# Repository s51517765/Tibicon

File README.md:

# Tibicon

## 概要 (Overview)

ATtiny202 を使ったマイコンボードで、コンセプトとしては小サイズ・低コストで、サイズは 19.0mm x 14.0mm となっています（バリを除く）。2024 年現在、市販されている Arduino 互換機の中で最小です（作者調べ）。

PCB 基板のほかに必要な部品コストは 170 円ほどです（秋月電子価格、送料を除く）。

### ピンアサイン

※書き込み用の UPDI_TX、UPDI_RX と Serial 通信用の TX(GPIO0)、RX(GPIO1)があります。

## 動作要件 (Requirements)

Arduino IDE
<br>　 Arduino IDE 1 系/2 系で動作確認済み
<br>ただし、ライブラリによっては動作しないものもあります。<br>
RAM が小さいので大規模なプログラムには向きません。

書き込みや Serial Print を使用するには USB シリアル変換モジュールが必要です。

## 部品リスト（Parts list）

| 部品                         | 種類           | 秋月コード           | 数量 |
| ---------------------------- | -------------- | -------------------- | ---- |
| 本 PCB                       | -              | -                    | 1    |
| AVR マイコン ATtiny202       | ATTINY202-SSNR | 115731               | 1    |
| ショットキーバリアダイオード | RB160M-30TR    | 101398               | 1    |
| 1608 抵抗                    | 1kΩ            | 111790               | 2    |
| 1608 抵抗                    | 470Ω           | 106471               | 1    |
| 1608LED                      | Green          | 111878               | 1    |
| 1608LED                      | Red            | 111879               | 1    |
| ピンヘッダ                   | オスまたはメス | 105779 または 100167 | 5x2  |

※ただし、抵抗は Amazon などでセットになったものを入手するほうが安いです

## 回路図（Schematics）

## 組み立て方 (Build guide)

LED とショットキーバリアダイオードは極性があります。
<br>抵抗は極性はありません。
<br>マイコン(ATtiny202)は 1 番ピンの向きに注意してください。

ピンヘッダは好みに応じて、メスピン・オスピン、上向き・下向きが選択可能です。
<br>ピンヘッダをはんだ付けするときは基板に対して垂直になるように気をつけてください。ピン 1 本だけ仮ではんだ付けをして正しく接触していることを確認するとよいです。

## 書き込み方法 (Writing method)

ATtiny202 を使用した本マイコンボードは、シリアル UPDI または jtag2updi で書き込みが可能ですが、本プロジェクトではシリアル UPDI を前提として設計しており、こちらを推奨します。
<br>※jtag2updi でも使用可能ですが、外付けの抵抗が必要です。
<br>　以下はシリアル UPDI での書き込み方法です。

### 書き込み時の接続

| 本マイコンボード | シリアル USB |
| ---------------- | ------------ |
| UPDI_TX          | TX ※         |
| UPDI_RX          | RX ※         |
| VCC              | VCC          |
| GND              | GND          |

### 書き込み手順

1.　 Arduino IDE のメニュー「ファイル ¥ 環境設定」より追加のボードマネージャに URL に「http://drazzy.com/package_drazzy.com_index.json」 を追加します。

2.　「ツール ¥ ボードマネージャ」より、「megaTinyCore」を追加します。

3.　「ツール」より、ボード情報を

- ボード:ATtiny412/402/212/202
- Chip:ATtiny202
- 書き込み装置:SerialUPDI - SLOW:57600 baud
  <br>のように変更します。

4.　メニューの「スケッチ ¥ 書き込み装置を使って書き込む」でスケッチを書き込みます。

Arduino IDE の 1 系ではいつもと同じようにスケッチを書き込みボタンを押下でも書き込むことが可能です。

## 使い方 (How to cording)

### L チカ

基本は Arduino と同様に使用できます。
<br>Builtin_LED（基板上の赤 LED）はピン番号 1 で使用できます。
<br>※緑 LED は電源ランプで、通電時に点灯します。

```
void setup() {
  pinMode(1, OUTPUT);
}

void loop() {
  digitalWrite(1, LOW);
  delay(1000);
  digitalWrite(1, HIGH);
  delay(1000);
}
```

ピン番号（GPIO）は 0 ～ 4 が使用可能です。

### PWM

本基板では GPIO0 ～ GPIO4 で PWM が使用できます。
<br>GPIO1 ～ GPIO04では通常の Arduino と同じ使い方で使用できますが、GPIO0 では以下のようにコーディングします。

```
void setup() {
  //GPIO0のセットアップ
  pinMode(0, OUTPUT);
  TCB0.CTRLA = TCB_ENABLE_bm | TCB_CLKSEL_CLKDIV1_gc; //start the timer, set the prescaler to 1
  TCB0.CTRLB = TCB_CCMPEN_bm | TCB_CNTMODE_PWM8_gc; //enable WO0, select the 8 bits PWM mode
  TCB0.CCMPL = 255; //set the PWM resolution to 8 bits
  TCB0.CCMPH = 0; //set the duty cycle
  //GPIO3のセットアップ
  pinMode(3, OUTPUT);
}

void loop()
{
  for (int i = 0; i < 256; i++)
  {
    //GPIO0のPWM
    TCB0.CCMPH = i;
    //GPIO3のPWM
    analogWrite(3,i);
    delay(10);
  }
}
```

### ADC(Analog Read)

本基板では GPIO1 ～ GPIO4 で ADC が使用できます。
<br>通常の Arduino と同じ使い方で使用できます。

```
void setup() {
  pinMode(1, OUTPUT);
  pinMode(4, INPUT);
}

void loop() {
  //ADC は1,2,3,4が使用可能
  int adc = analogRead(4);
  analogWrite(1, adc);
}
```

### Serial print の使い方

USB シリアル変換は内蔵していませんので、外部の USB シリアル変換を使います。

#### USB シリアル使用時の接続

| 本マイコンボード | シリアル USB |
| ---------------- | ------------ |
| TX(GPIO0)        | RX           |
| RX(GPIO1)        | TX           |

※図は基板電源をUSBシリアルから給電する場合

Teraterm などで読み取ることができます。Arduino IDE でも読み取ることはできますが、書き込み時と接続が異なりますので USB シリアルの繋ぎ変えが必要になります。
<br>※D1 ピン（Builtin LED）と D2 ピンを共有しているため Serial と同時に使うことはできません。

## サンプルコード（Sample Code）

[sample フォルダ](/sample/)を参照ください。

## ブートローダーの書き込み (How to write bootloader)

マイコンがおかしくなった時やブートローダーが書き込まれていないマイコンを購入した場合は書き込みが必要になります。Arduino IDE で書き込むことが出来ます。
<br>通常は必要ありません。

## ライセンス (License)

This software is released under the MIT License, see LICENSE.

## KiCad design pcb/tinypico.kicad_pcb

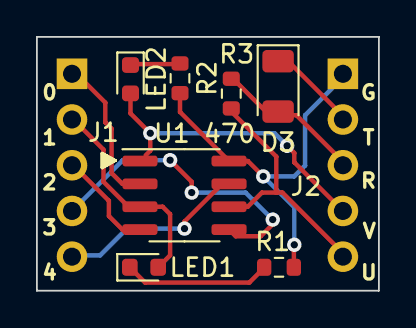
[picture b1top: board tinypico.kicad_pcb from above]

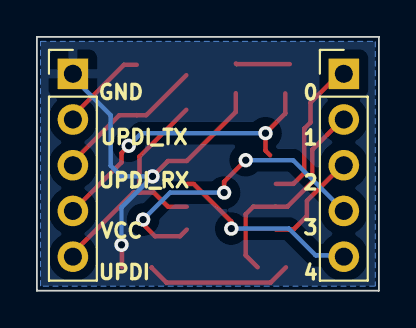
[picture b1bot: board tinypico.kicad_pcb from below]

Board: 2 copper layers, 19.0 x 14.1 mm, 9 parts (2 on the bottom side), 12 nets.

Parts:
470: R3; R_0603_1608Metric
D3: RB160M-30; D_1206_3216Metric
J1, J2: Conn_01x05_Pin; PinHeader_1x05_P2.54mm_Vertical
LED1: LED_G; D_0603_1608Metric
LED2: LED_R; D_0603_1608Metric
R1, R2: 1k; R_0603_1608Metric
U1: ATtiny202-SS; SOIC-8_3.9x4.9mm_P1.27mm

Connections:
1: J2.4, LED2.2 (A), U1.1 (VCC)
2: J1.1, U1.2 (PA6)
3: J1.2, LED1.2 (A), U1.3 (PA7)
4: J1.3, U1.4 (PA1)
5: J1.4, U1.5 (PA2)
6: 470.1, J2.5, U1.6 (~RESET/PA0)
7: J1.5, U1.7 (PA3)
8: J2.1, R1.2, R2.2, U1.8 (GND)
unnamed: LED1.1 (K), R1.1
unnamed: LED2.1 (K), R2.1
UPDI_RX: 470.2, D3.2 (A), J2.3
UPDI_TX: D3.1 (K), J2.2

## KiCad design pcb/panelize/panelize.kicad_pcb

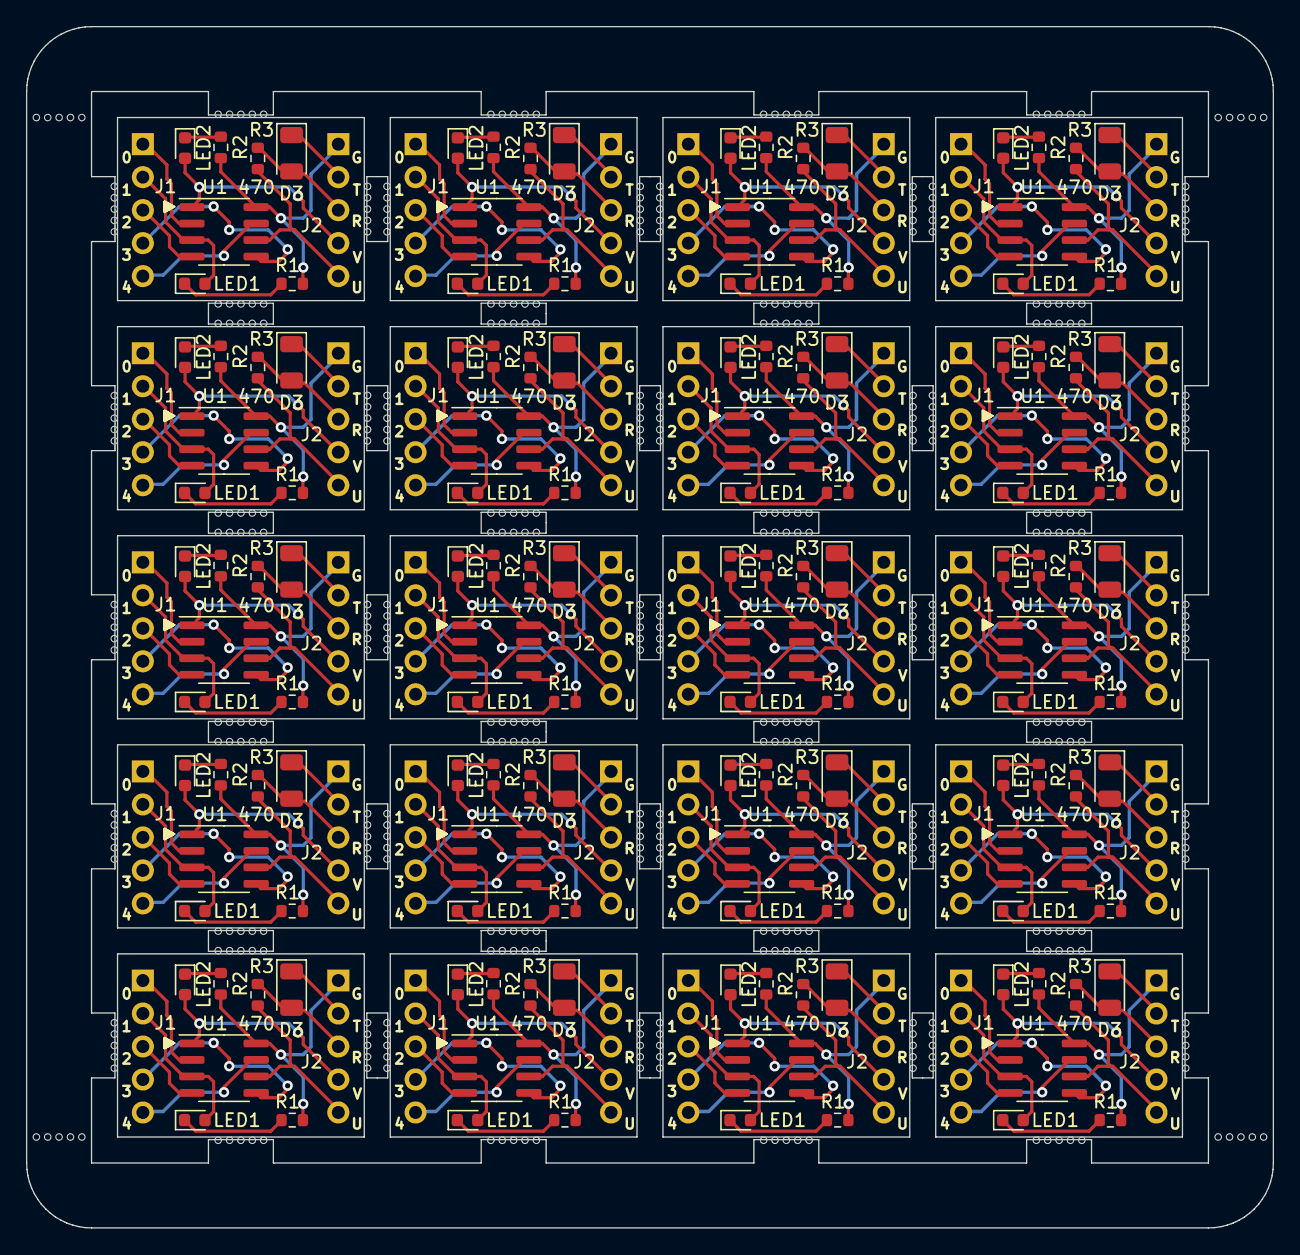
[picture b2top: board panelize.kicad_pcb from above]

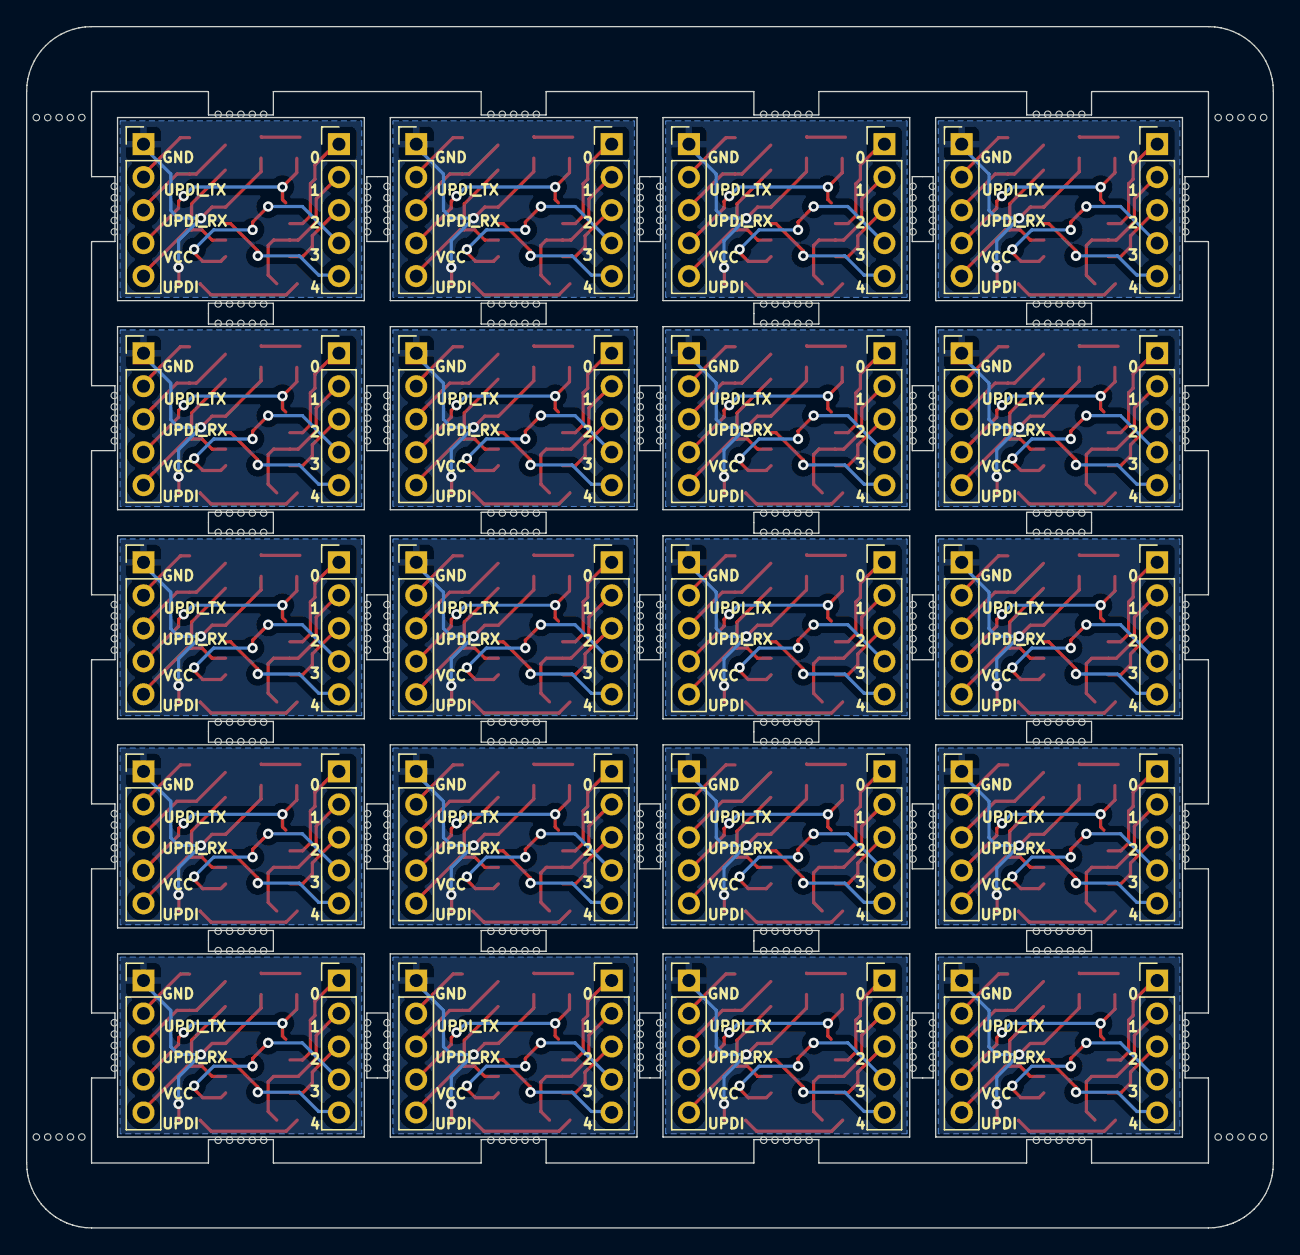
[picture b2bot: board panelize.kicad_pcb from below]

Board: 2 copper layers, 96.0 x 92.5 mm, 600 parts (40 on the bottom side), 240 nets.

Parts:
470, 470#2, 470#3, 470#4, 470#5, 470#6, 470#7, 470#8, 470#9, 470#10, 470#11, 470#12, 470#13, 470#14, 470#15, 470#16, 470#17, 470#18, 470#19, 470#20: R3; R_0603_1608Metric
D3, D3#2, D3#3, D3#4, D3#5, D3#6, D3#7, D3#8, D3#9, D3#10, D3#11, D3#12, D3#13, D3#14, D3#15, D3#16, D3#17, D3#18, D3#19, D3#20: RB160M-30; D_1206_3216Metric
J1, J1#2, J1#3, J1#4, J1#5, J1#6, J1#7, J1#8, J1#9, J1#10, J1#11, J1#12, J1#13, J1#14, J1#15, J1#16, J1#17, J1#18, J1#19, J1#20, J2, J2#2, J2#3, J2#4, J2#5, J2#6, J2#7, J2#8, J2#9, J2#10, J2#11, J2#12, J2#13, J2#14, J2#15, J2#16, J2#17, J2#18, J2#19, J2#20: Conn_01x05_Pin; PinHeader_1x05_P2.54mm_Vertical
KiKit_MB_1_3, KiKit_MB_1_4, KiKit_MB_1_5, KiKit_MB_1_6, KiKit_MB_1_7, KiKit_MB_2_3, KiKit_MB_2_4, KiKit_MB_2_5, KiKit_MB_2_6, KiKit_MB_2_7, KiKit_MB_3_3, KiKit_MB_3_4, KiKit_MB_3_5, KiKit_MB_3_6, KiKit_MB_3_7, KiKit_MB_4_3, KiKit_MB_4_4, KiKit_MB_4_5, KiKit_MB_4_6, KiKit_MB_4_7, KiKit_MB_5_3, KiKit_MB_5_4, KiKit_MB_5_5, KiKit_MB_5_6, KiKit_MB_5_7, KiKit_MB_6_3, KiKit_MB_6_4, KiKit_MB_6_5, KiKit_MB_6_6, KiKit_MB_6_7, KiKit_MB_7_3, KiKit_MB_7_4, KiKit_MB_7_5, KiKit_MB_7_6, KiKit_MB_7_7, KiKit_MB_8_3, KiKit_MB_8_4, KiKit_MB_8_5, KiKit_MB_8_6, KiKit_MB_8_7, KiKit_MB_9_3, KiKit_MB_9_4, KiKit_MB_9_5, KiKit_MB_9_6, KiKit_MB_9_7, KiKit_MB_10_3, KiKit_MB_10_4, KiKit_MB_10_5, KiKit_MB_10_6, KiKit_MB_10_7, KiKit_MB_11_3, KiKit_MB_11_4, KiKit_MB_11_5, KiKit_MB_11_6, KiKit_MB_11_7, KiKit_MB_12_3, KiKit_MB_12_4, KiKit_MB_12_5, KiKit_MB_12_6, KiKit_MB_12_7, KiKit_MB_13_3, KiKit_MB_13_4, KiKit_MB_13_5, KiKit_MB_13_6, KiKit_MB_13_7, KiKit_MB_14_3, KiKit_MB_14_4, KiKit_MB_14_5, KiKit_MB_14_6, KiKit_MB_14_7, KiKit_MB_15_3, KiKit_MB_15_4, KiKit_MB_15_5, KiKit_MB_15_6, KiKit_MB_15_7, KiKit_MB_16_3, KiKit_MB_16_4, KiKit_MB_16_5, KiKit_MB_16_6, KiKit_MB_16_7, KiKit_MB_17_3, KiKit_MB_17_4, KiKit_MB_17_5, KiKit_MB_17_6, KiKit_MB_17_7, KiKit_MB_18_3, KiKit_MB_18_4, KiKit_MB_18_5, KiKit_MB_18_6, KiKit_MB_18_7, KiKit_MB_19_3, KiKit_MB_19_4, KiKit_MB_19_5, KiKit_MB_19_6, KiKit_MB_19_7, KiKit_MB_20_3, KiKit_MB_20_4, KiKit_MB_20_5, KiKit_MB_20_6, KiKit_MB_20_7, KiKit_MB_21_3, KiKit_MB_21_4, KiKit_MB_21_5, KiKit_MB_21_6, KiKit_MB_21_7, KiKit_MB_22_3, KiKit_MB_22_4, KiKit_MB_22_5, KiKit_MB_22_6, KiKit_MB_22_7, KiKit_MB_23_3, KiKit_MB_23_4, KiKit_MB_23_5, KiKit_MB_23_6, KiKit_MB_23_7, KiKit_MB_24_3, KiKit_MB_24_4, KiKit_MB_24_5, KiKit_MB_24_6, KiKit_MB_24_7, KiKit_MB_25_3, KiKit_MB_25_4, KiKit_MB_25_5, KiKit_MB_25_6, KiKit_MB_25_7, KiKit_MB_26_3, KiKit_MB_26_4, KiKit_MB_26_5, KiKit_MB_26_6, KiKit_MB_26_7, KiKit_MB_27_3, KiKit_MB_27_4, KiKit_MB_27_5, KiKit_MB_27_6, KiKit_MB_27_7, KiKit_MB_28_3, KiKit_MB_28_4, KiKit_MB_28_5, KiKit_MB_28_6, KiKit_MB_28_7, KiKit_MB_29_3, KiKit_MB_29_4, KiKit_MB_29_5, KiKit_MB_29_6, KiKit_MB_29_7, KiKit_MB_30_3, KiKit_MB_30_4, KiKit_MB_30_5, KiKit_MB_30_6, KiKit_MB_30_7, KiKit_MB_31_3, KiKit_MB_31_4, KiKit_MB_31_5, KiKit_MB_31_6, KiKit_MB_31_7, KiKit_MB_32_3, KiKit_MB_32_4, KiKit_MB_32_5, KiKit_MB_32_6, KiKit_MB_32_7, KiKit_MB_33_3, KiKit_MB_33_4, KiKit_MB_33_5, KiKit_MB_33_6, KiKit_MB_33_7, KiKit_MB_34_3, KiKit_MB_34_4, KiKit_MB_34_5, KiKit_MB_34_6, KiKit_MB_34_7, KiKit_MB_35_3, KiKit_MB_35_4, KiKit_MB_35_5, KiKit_MB_35_6, KiKit_MB_35_7, KiKit_MB_36_3, KiKit_MB_36_4, KiKit_MB_36_5, KiKit_MB_36_6, KiKit_MB_36_7, KiKit_MB_37_3, KiKit_MB_37_4, KiKit_MB_37_5, KiKit_MB_37_6, KiKit_MB_37_7, KiKit_MB_38_3, KiKit_MB_38_4, KiKit_MB_38_5, KiKit_MB_38_6, KiKit_MB_38_7, KiKit_MB_39_3, KiKit_MB_39_4, KiKit_MB_39_5, KiKit_MB_39_6, KiKit_MB_39_7, KiKit_MB_40_3, KiKit_MB_40_4, KiKit_MB_40_5, KiKit_MB_40_6, KiKit_MB_40_7, KiKit_MB_41_3, KiKit_MB_41_4, KiKit_MB_41_5, KiKit_MB_41_6, KiKit_MB_41_7, KiKit_MB_42_3, KiKit_MB_42_4, KiKit_MB_42_5, KiKit_MB_42_6, KiKit_MB_42_7, KiKit_MB_43_3, KiKit_MB_43_4, KiKit_MB_43_5, KiKit_MB_43_6, KiKit_MB_43_7, KiKit_MB_44_3, KiKit_MB_44_4, KiKit_MB_44_5, KiKit_MB_44_6, KiKit_MB_44_7, KiKit_MB_45_3, KiKit_MB_45_4, KiKit_MB_45_5, KiKit_MB_45_6, KiKit_MB_45_7, KiKit_MB_46_3, KiKit_MB_46_4, KiKit_MB_46_5, KiKit_MB_46_6, KiKit_MB_46_7, KiKit_MB_47_3, KiKit_MB_47_4, KiKit_MB_47_5, KiKit_MB_47_6, KiKit_MB_47_7, KiKit_MB_48_3, KiKit_MB_48_4, KiKit_MB_48_5, KiKit_MB_48_6, KiKit_MB_48_7, KiKit_MB_49_3, KiKit_MB_49_4, KiKit_MB_49_5, KiKit_MB_49_6, KiKit_MB_49_7, KiKit_MB_50_3, KiKit_MB_50_4, KiKit_MB_50_5, KiKit_MB_50_6, KiKit_MB_50_7, KiKit_MB_51_3, KiKit_MB_51_4, KiKit_MB_51_5, KiKit_MB_51_6, KiKit_MB_51_7, KiKit_MB_52_3, KiKit_MB_52_4, KiKit_MB_52_5, KiKit_MB_52_6, KiKit_MB_52_7, KiKit_MB_53_3, KiKit_MB_53_4, KiKit_MB_53_5, KiKit_MB_53_6, KiKit_MB_53_7, KiKit_MB_54_3, KiKit_MB_54_4, KiKit_MB_54_5, KiKit_MB_54_6, KiKit_MB_54_7, KiKit_MB_55_3, KiKit_MB_55_4, KiKit_MB_55_5, KiKit_MB_55_6, KiKit_MB_55_7, KiKit_MB_56_3, KiKit_MB_56_4, KiKit_MB_56_5, KiKit_MB_56_6, KiKit_MB_56_7, KiKit_MB_57_3, KiKit_MB_57_4, KiKit_MB_57_5, KiKit_MB_57_6, KiKit_MB_57_7, KiKit_MB_58_3, KiKit_MB_58_4, KiKit_MB_58_5, KiKit_MB_58_6, KiKit_MB_58_7, KiKit_MB_59_3, KiKit_MB_59_4, KiKit_MB_59_5, KiKit_MB_59_6, KiKit_MB_59_7, KiKit_MB_60_3, KiKit_MB_60_4, KiKit_MB_60_5, KiKit_MB_60_6, KiKit_MB_60_7, KiKit_MB_61_3, KiKit_MB_61_4, KiKit_MB_61_5, KiKit_MB_61_6, KiKit_MB_61_7, KiKit_MB_62_3, KiKit_MB_62_4, KiKit_MB_62_5, KiKit_MB_62_6, KiKit_MB_62_7, KiKit_MB_63_3, KiKit_MB_63_4, KiKit_MB_63_5, KiKit_MB_63_6, KiKit_MB_63_7, KiKit_MB_64_3, KiKit_MB_64_4, KiKit_MB_64_5, KiKit_MB_64_6, KiKit_MB_64_7, KiKit_MB_65_3, KiKit_MB_65_4, KiKit_MB_65_5, KiKit_MB_65_6, KiKit_MB_65_7, KiKit_MB_66_3, KiKit_MB_66_4, KiKit_MB_66_5, KiKit_MB_66_6, KiKit_MB_66_7, KiKit_MB_67_3, KiKit_MB_67_4, KiKit_MB_67_5, KiKit_MB_67_6, KiKit_MB_67_7, KiKit_MB_68_3, KiKit_MB_68_4, KiKit_MB_68_5, KiKit_MB_68_6, KiKit_MB_68_7, KiKit_MB_69_3, KiKit_MB_69_4, KiKit_MB_69_5, KiKit_MB_69_6, KiKit_MB_69_7, KiKit_MB_70_3, KiKit_MB_70_4, KiKit_MB_70_5, KiKit_MB_70_6, KiKit_MB_70_7, KiKit_MB_71_3, KiKit_MB_71_4, KiKit_MB_71_5, KiKit_MB_71_6, KiKit_MB_71_7, KiKit_MB_72_3, KiKit_MB_72_4, KiKit_MB_72_5, KiKit_MB_72_6, KiKit_MB_72_7, KiKit_MB_73_3, KiKit_MB_73_4, KiKit_MB_73_5, KiKit_MB_73_6, KiKit_MB_73_7, KiKit_MB_74_3, KiKit_MB_74_4, KiKit_MB_74_5, KiKit_MB_74_6, KiKit_MB_74_7, KiKit_MB_75_3, KiKit_MB_75_4, KiKit_MB_75_5, KiKit_MB_75_6, KiKit_MB_75_7, KiKit_MB_76_3, KiKit_MB_76_4, KiKit_MB_76_5, KiKit_MB_76_6, KiKit_MB_76_7, KiKit_MB_77_3, KiKit_MB_77_4, KiKit_MB_77_5, KiKit_MB_77_6, KiKit_MB_77_7, KiKit_MB_78_3, KiKit_MB_78_4, KiKit_MB_78_5, KiKit_MB_78_6, KiKit_MB_78_7, KiKit_MB_79_3, KiKit_MB_79_4, KiKit_MB_79_5, KiKit_MB_79_6, KiKit_MB_79_7, KiKit_MB_80_3, KiKit_MB_80_4, KiKit_MB_80_5, KiKit_MB_80_6, KiKit_MB_80_7, KiKit_MB_81_3, KiKit_MB_81_4, KiKit_MB_81_5, KiKit_MB_81_6, KiKit_MB_81_7, KiKit_MB_82_3, KiKit_MB_82_4, KiKit_MB_82_5, KiKit_MB_82_6, KiKit_MB_82_7, KiKit_MB_83_3, KiKit_MB_83_4, KiKit_MB_83_5, KiKit_MB_83_6, KiKit_MB_83_7, KiKit_MB_84_3, KiKit_MB_84_4, KiKit_MB_84_5, KiKit_MB_84_6, KiKit_MB_84_7: NPTH
LED1, LED1#2, LED1#3, LED1#4, LED1#5, LED1#6, LED1#7, LED1#8, LED1#9, LED1#10, LED1#11, LED1#12, LED1#13, LED1#14, LED1#15, LED1#16, LED1#17, LED1#18, LED1#19, LED1#20: LED_G; D_0603_1608Metric
LED2, LED2#2, LED2#3, LED2#4, LED2#5, LED2#6, LED2#7, LED2#8, LED2#9, LED2#10, LED2#11, LED2#12, LED2#13, LED2#14, LED2#15, LED2#16, LED2#17, LED2#18, LED2#19, LED2#20: LED_R; D_0603_1608Metric
R1, R1#2, R1#3, R1#4, R1#5, R1#6, R1#7, R1#8, R1#9, R1#10, R1#11, R1#12, R1#13, R1#14, R1#15, R1#16, R1#17, R1#18, R1#19, R1#20, R2, R2#2, R2#3, R2#4, R2#5, R2#6, R2#7, R2#8, R2#9, R2#10, R2#11, R2#12, R2#13, R2#14, R2#15, R2#16, R2#17, R2#18, R2#19, R2#20: 1k; R_0603_1608Metric
U1, U1#2, U1#3, U1#4, U1#5, U1#6, U1#7, U1#8, U1#9, U1#10, U1#11, U1#12, U1#13, U1#14, U1#15, U1#16, U1#17, U1#18, U1#19, U1#20: ATtiny202-SS; SOIC-8_3.9x4.9mm_P1.27mm

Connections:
Board_0-1: J2#12.4, LED2#11.2 (A), U1#4.1 (VCC)
Board_0-2: J1#14.1, U1#4.2 (PA6)
Board_0-3: J1#14.2, LED1#4.2 (A), U1#4.3 (PA7)
Board_0-4: J1#14.3, U1#4.4 (PA1)
Board_0-5: J1#14.4, U1#4.5 (PA2)
Board_0-6: 470#19.1, J2#12.5, U1#4.6 (~RESET/PA0)
Board_0-7: J1#14.5, U1#4.7 (PA3)
Board_0-8: J2#12.1, R1#11.2, R2#15.2, U1#4.8 (GND)
Board_0-Net-(LED1-K): LED1#4.1 (K), R1#11.1
Board_0-Net-(LED2-K): LED2#11.1 (K), R2#15.1
Board_0-UPDI_RX: 470#19.2, D3#20.2 (A), J2#12.3
Board_0-UPDI_TX: D3#20.1 (K), J2#12.2
Board_1-1: J2#7.4, LED2#4.2 (A), U1#8.1 (VCC)
Board_1-2: J1#4.1, U1#8.2 (PA6)
Board_1-3: J1#4.2, LED1#15.2 (A), U1#8.3 (PA7)
Board_1-4: J1#4.3, U1#8.4 (PA1)
Board_1-5: J1#4.4, U1#8.5 (PA2)
Board_1-6: 470#20.1, J2#7.5, U1#8.6 (~RESET/PA0)
Board_1-7: J1#4.5, U1#8.7 (PA3)
Board_1-8: J2#7.1, R1#4.2, R2#11.2, U1#8.8 (GND)
Board_1-Net-(LED1-K): LED1#15.1 (K), R1#4.1
Board_1-Net-(LED2-K): LED2#4.1 (K), R2#11.1
Board_1-UPDI_RX: 470#20.2, D3#18.2 (A), J2#7.3
Board_1-UPDI_TX: D3#18.1 (K), J2#7.2
Board_2-1: J2#2.4, LED2#9.2 (A), U1#15.1 (VCC)
Board_2-2: J1.1, U1#15.2 (PA6)
Board_2-3: J1.2, LED1#19.2 (A), U1#15.3 (PA7)
Board_2-4: J1.3, U1#15.4 (PA1)
Board_2-5: J1.4, U1#15.5 (PA2)
Board_2-6: 470#2.1, J2#2.5, U1#15.6 (~RESET/PA0)
Board_2-7: J1.5, U1#15.7 (PA3)
Board_2-8: J2#2.1, R1#7.2, R2#9.2, U1#15.8 (GND)
Board_2-Net-(LED1-K): LED1#19.1 (K), R1#7.1
Board_2-Net-(LED2-K): LED2#9.1 (K), R2#9.1
Board_2-UPDI_RX: 470#2.2, D3#4.2 (A), J2#2.3
Board_2-UPDI_TX: D3#4.1 (K), J2#2.2
Board_3-1: J2#15.4, LED2.2 (A), U1#6.1 (VCC)
Board_3-2: J1#6.1, U1#6.2 (PA6)
Board_3-3: J1#6.2, LED1#2.2 (A), U1#6.3 (PA7)
Board_3-4: J1#6.3, U1#6.4 (PA1)
Board_3-5: J1#6.4, U1#6.5 (PA2)
Board_3-6: 470#13.1, J2#15.5, U1#6.6 (~RESET/PA0)
Board_3-7: J1#6.5, U1#6.7 (PA3)
Board_3-8: J2#15.1, R1#17.2, R2#16.2, U1#6.8 (GND)
Board_3-Net-(LED1-K): LED1#2.1 (K), R1#17.1
Board_3-Net-(LED2-K): LED2.1 (K), R2#16.1
Board_3-UPDI_RX: 470#13.2, D3.2 (A), J2#15.3
Board_3-UPDI_TX: D3.1 (K), J2#15.2
Board_4-1: J2#20.4, LED2#17.2 (A), U1#16.1 (VCC)
Board_4-2: J1#5.1, U1#16.2 (PA6)
Board_4-3: J1#5.2, LED1#3.2 (A), U1#16.3 (PA7)
Board_4-4: J1#5.3, U1#16.4 (PA1)
Board_4-5: J1#5.4, U1#16.5 (PA2)
Board_4-6: 470#9.1, J2#20.5, U1#16.6 (~RESET/PA0)
Board_4-7: J1#5.5, U1#16.7 (PA3)
Board_4-8: J2#20.1, R1#6.2, R2#8.2, U1#16.8 (GND)
Board_4-Net-(LED1-K): LED1#3.1 (K), R1#6.1
Board_4-Net-(LED2-K): LED2#17.1 (K), R2#8.1
Board_4-UPDI_RX: 470#9.2, D3#14.2 (A), J2#20.3
Board_4-UPDI_TX: D3#14.1 (K), J2#20.2
Board_5-1: J2#18.4, LED2#14.2 (A), U1#13.1 (VCC)
Board_5-2: J1#13.1, U1#13.2 (PA6)
Board_5-3: J1#13.2, LED1#12.2 (A), U1#13.3 (PA7)
Board_5-4: J1#13.3, U1#13.4 (PA1)
Board_5-5: J1#13.4, U1#13.5 (PA2)
Board_5-6: 470#12.1, J2#18.5, U1#13.6 (~RESET/PA0)
Board_5-7: J1#13.5, U1#13.7 (PA3)
Board_5-8: J2#18.1, R1#16.2, R2#2.2, U1#13.8 (GND)
Board_5-Net-(LED1-K): LED1#12.1 (K), R1#16.1
Board_5-Net-(LED2-K): LED2#14.1 (K), R2#2.1
Board_5-UPDI_RX: 470#12.2, D3#3.2 (A), J2#18.3
Board_5-UPDI_TX: D3#3.1 (K), J2#18.2
Board_6-1: J2#17.4, LED2#3.2 (A), U1#9.1 (VCC)
Board_6-2: J1#10.1, U1#9.2 (PA6)
Board_6-3: J1#10.2, LED1#10.2 (A), U1#9.3 (PA7)
Board_6-4: J1#10.3, U1#9.4 (PA1)
Board_6-5: J1#10.4, U1#9.5 (PA2)
Board_6-6: 470#5.1, J2#17.5, U1#9.6 (~RESET/PA0)
Board_6-7: J1#10.5, U1#9.7 (PA3)
Board_6-8: J2#17.1, R1#13.2, R2#17.2, U1#9.8 (GND)
Board_6-Net-(LED1-K): LED1#10.1 (K), R1#13.1
Board_6-Net-(LED2-K): LED2#3.1 (K), R2#17.1
Board_6-UPDI_RX: 470#5.2, D3#12.2 (A), J2#17.3
Board_6-UPDI_TX: D3#12.1 (K), J2#17.2
Board_7-1: J2#4.4, LED2#15.2 (A), U1#11.1 (VCC)
Board_7-2: J1#7.1, U1#11.2 (PA6)
Board_7-3: J1#7.2, LED1#5.2 (A), U1#11.3 (PA7)
Board_7-4: J1#7.3, U1#11.4 (PA1)
Board_7-5: J1#7.4, U1#11.5 (PA2)
Board_7-6: 470#11.1, J2#4.5, U1#11.6 (~RESET/PA0)
Board_7-7: J1#7.5, U1#11.7 (PA3)
Board_7-8: J2#4.1, R1#12.2, R2#5.2, U1#11.8 (GND)
Board_7-Net-(LED1-K): LED1#5.1 (K), R1#12.1
Board_7-Net-(LED2-K): LED2#15.1 (K), R2#5.1
Board_7-UPDI_RX: 470#11.2, D3#2.2 (A), J2#4.3
Board_7-UPDI_TX: D3#2.1 (K), J2#4.2
Board_8-1: J2#19.4, LED2#5.2 (A), U1#5.1 (VCC)
Board_8-2: J1#16.1, U1#5.2 (PA6)
Board_8-3: J1#16.2, LED1#20.2 (A), U1#5.3 (PA7)
Board_8-4: J1#16.3, U1#5.4 (PA1)
Board_8-5: J1#16.4, U1#5.5 (PA2)
Board_8-6: 470#3.1, J2#19.5, U1#5.6 (~RESET/PA0)
Board_8-7: J1#16.5, U1#5.7 (PA3)
Board_8-8: J2#19.1, R1#2.2, R2#6.2, U1#5.8 (GND)
Board_8-Net-(LED1-K): LED1#20.1 (K), R1#2.1
Board_8-Net-(LED2-K): LED2#5.1 (K), R2#6.1
Board_8-UPDI_RX: 470#3.2, D3#10.2 (A), J2#19.3
Board_8-UPDI_TX: D3#10.1 (K), J2#19.2
Board_9-1: J2#9.4, LED2#2.2 (A), U1#18.1 (VCC)
Board_9-2: J1#20.1, U1#18.2 (PA6)
Board_9-3: J1#20.2, LED1#18.2 (A), U1#18.3 (PA7)
Board_9-4: J1#20.3, U1#18.4 (PA1)
Board_9-5: J1#20.4, U1#18.5 (PA2)
Board_9-6: 470#14.1, J2#9.5, U1#18.6 (~RESET/PA0)
Board_9-7: J1#20.5, U1#18.7 (PA3)
Board_9-8: J2#9.1, R1#3.2, R2#14.2, U1#18.8 (GND)
Board_9-Net-(LED1-K): LED1#18.1 (K), R1#3.1
Board_9-Net-(LED2-K): LED2#2.1 (K), R2#14.1
Board_9-UPDI_RX: 470#14.2, D3#8.2 (A), J2#9.3
Board_9-UPDI_TX: D3#8.1 (K), J2#9.2
Board_10-1: J2#10.4, LED2#8.2 (A), U1#17.1 (VCC)
Board_10-2: J1#12.1, U1#17.2 (PA6)
Board_10-3: J1#12.2, LED1#17.2 (A), U1#17.3 (PA7)
Board_10-4: J1#12.3, U1#17.4 (PA1)
Board_10-5: J1#12.4, U1#17.5 (PA2)
Board_10-6: 470#8.1, J2#10.5, U1#17.6 (~RESET/PA0)
Board_10-7: J1#12.5, U1#17.7 (PA3)
Board_10-8: J2#10.1, R1#9.2, R2#4.2, U1#17.8 (GND)
Board_10-Net-(LED1-K): LED1#17.1 (K), R1#9.1
Board_10-Net-(LED2-K): LED2#8.1 (K), R2#4.1
Board_10-UPDI_RX: 470#8.2, D3#11.2 (A), J2#10.3
Board_10-UPDI_TX: D3#11.1 (K), J2#10.2
Board_11-1: J2#14.4, LED2#16.2 (A), U1#3.1 (VCC)
Board_11-2: J1#8.1, U1#3.2 (PA6)
Board_11-3: J1#8.2, LED1.2 (A), U1#3.3 (PA7)
Board_11-4: J1#8.3, U1#3.4 (PA1)
Board_11-5: J1#8.4, U1#3.5 (PA2)
Board_11-6: 470#18.1, J2#14.5, U1#3.6 (~RESET/PA0)
Board_11-7: J1#8.5, U1#3.7 (PA3)
Board_11-8: J2#14.1, R1.2, R2#10.2, U1#3.8 (GND)
Board_11-Net-(LED1-K): LED1.1 (K), R1.1
Board_11-Net-(LED2-K): LED2#16.1 (K), R2#10.1
Board_11-UPDI_RX: 470#18.2, D3#6.2 (A), J2#14.3
Board_11-UPDI_TX: D3#6.1 (K), J2#14.2
Board_12-1: J2#3.4, LED2#7.2 (A), U1#14.1 (VCC)
Board_12-2: J1#9.1, U1#14.2 (PA6)
Board_12-3: J1#9.2, LED1#7.2 (A), U1#14.3 (PA7)
Board_12-4: J1#9.3, U1#14.4 (PA1)
Board_12-5: J1#9.4, U1#14.5 (PA2)
Board_12-6: 470#4.1, J2#3.5, U1#14.6 (~RESET/PA0)
Board_12-7: J1#9.5, U1#14.7 (PA3)
Board_12-8: J2#3.1, R1#10.2, R2#18.2, U1#14.8 (GND)
Board_12-Net-(LED1-K): LED1#7.1 (K), R1#10.1
Board_12-Net-(LED2-K): LED2#7.1 (K), R2#18.1
Board_12-UPDI_RX: 470#4.2, D3#7.2 (A), J2#3.3
Board_12-UPDI_TX: D3#7.1 (K), J2#3.2
Board_13-1: J2#11.4, LED2#13.2 (A), U1#7.1 (VCC)
Board_13-2: J1#3.1, U1#7.2 (PA6)
Board_13-3: J1#3.2, LED1#9.2 (A), U1#7.3 (PA7)
Board_13-4: J1#3.3, U1#7.4 (PA1)
Board_13-5: J1#3.4, U1#7.5 (PA2)
Board_13-6: 470#6.1, J2#11.5, U1#7.6 (~RESET/PA0)
Board_13-7: J1#3.5, U1#7.7 (PA3)
Board_13-8: J2#11.1, R1#8.2, R2#13.2, U1#7.8 (GND)
Board_13-Net-(LED1-K): LED1#9.1 (K), R1#8.1
Board_13-Net-(LED2-K): LED2#13.1 (K), R2#13.1
Board_13-UPDI_RX: 470#6.2, D3#16.2 (A), J2#11.3
Board_13-UPDI_TX: D3#16.1 (K), J2#11.2
Board_14-1: J2#6.4, LED2#10.2 (A), U1#19.1 (VCC)
Board_14-2: J1#2.1, U1#19.2 (PA6)
Board_14-3: J1#2.2, LED1#6.2 (A), U1#19.3 (PA7)
Board_14-4: J1#2.3, U1#19.4 (PA1)
Board_14-5: J1#2.4, U1#19.5 (PA2)
Board_14-6: 470#7.1, J2#6.5, U1#19.6 (~RESET/PA0)
Board_14-7: J1#2.5, U1#19.7 (PA3)
Board_14-8: J2#6.1, R1#5.2, R2#20.2, U1#19.8 (GND)
Board_14-Net-(LED1-K): LED1#6.1 (K), R1#5.1
Board_14-Net-(LED2-K): LED2#10.1 (K), R2#20.1
Board_14-UPDI_RX: 470#7.2, D3#13.2 (A), J2#6.3
Board_14-UPDI_TX: D3#13.1 (K), J2#6.2
Board_15-1: J2#13.4, LED2#19.2 (A), U1#10.1 (VCC)
Board_15-2: J1#18.1, U1#10.2 (PA6)
Board_15-3: J1#18.2, LED1#14.2 (A), U1#10.3 (PA7)
Board_15-4: J1#18.3, U1#10.4 (PA1)
Board_15-5: J1#18.4, U1#10.5 (PA2)
Board_15-6: 470#16.1, J2#13.5, U1#10.6 (~RESET/PA0)
Board_15-7: J1#18.5, U1#10.7 (PA3)
Board_15-8: J2#13.1, R1#14.2, R2#12.2, U1#10.8 (GND)
Board_15-Net-(LED1-K): LED1#14.1 (K), R1#14.1
Board_15-Net-(LED2-K): LED2#19.1 (K), R2#12.1
Board_15-UPDI_RX: 470#16.2, D3#19.2 (A), J2#13.3
Board_15-UPDI_TX: D3#19.1 (K), J2#13.2
Board_16-1: J2#5.4, LED2#20.2 (A), U1#2.1 (VCC)
Board_16-2: J1#11.1, U1#2.2 (PA6)
Board_16-3: J1#11.2, LED1#13.2 (A), U1#2.3 (PA7)
Board_16-4: J1#11.3, U1#2.4 (PA1)
Board_16-5: J1#11.4, U1#2.5 (PA2)
Board_16-6: 470#15.1, J2#5.5, U1#2.6 (~RESET/PA0)
Board_16-7: J1#11.5, U1#2.7 (PA3)
Board_16-8: J2#5.1, R1#15.2, R2#7.2, U1#2.8 (GND)
Board_16-Net-(LED1-K): LED1#13.1 (K), R1#15.1
Board_16-Net-(LED2-K): LED2#20.1 (K), R2#7.1
Board_16-UPDI_RX: 470#15.2, D3#5.2 (A), J2#5.3
Board_16-UPDI_TX: D3#5.1 (K), J2#5.2
Board_17-1: J2.4, LED2#18.2 (A), U1#12.1 (VCC)
Board_17-2: J1#17.1, U1#12.2 (PA6)
Board_17-3: J1#17.2, LED1#16.2 (A), U1#12.3 (PA7)
Board_17-4: J1#17.3, U1#12.4 (PA1)
Board_17-5: J1#17.4, U1#12.5 (PA2)
Board_17-6: 470#10.1, J2.5, U1#12.6 (~RESET/PA0)
Board_17-7: J1#17.5, U1#12.7 (PA3)
Board_17-8: J2.1, R1#18.2, R2#3.2, U1#12.8 (GND)
Board_17-Net-(LED1-K): LED1#16.1 (K), R1#18.1
Board_17-Net-(LED2-K): LED2#18.1 (K), R2#3.1
Board_17-UPDI_RX: 470#10.2, D3#15.2 (A), J2.3
Board_17-UPDI_TX: D3#15.1 (K), J2.2
Board_18-1: J2#8.4, LED2#6.2 (A), U1.1 (VCC)
Board_18-2: J1#19.1, U1.2 (PA6)
Board_18-3: J1#19.2, LED1#11.2 (A), U1.3 (PA7)
Board_18-4: J1#19.3, U1.4 (PA1)
Board_18-5: J1#19.4, U1.5 (PA2)
Board_18-6: 470.1, J2#8.5, U1.6 (~RESET/PA0)
Board_18-7: J1#19.5, U1.7 (PA3)
Board_18-8: J2#8.1, R1#19.2, R2.2, U1.8 (GND)
Board_18-Net-(LED1-K): LED1#11.1 (K), R1#19.1
Board_18-Net-(LED2-K): LED2#6.1 (K), R2.1
Board_18-UPDI_RX: 470.2, D3#17.2 (A), J2#8.3
Board_18-UPDI_TX: D3#17.1 (K), J2#8.2
Board_19-1: J2#16.4, LED2#12.2 (A), U1#20.1 (VCC)
Board_19-2: J1#15.1, U1#20.2 (PA6)
Board_19-3: J1#15.2, LED1#8.2 (A), U1#20.3 (PA7)
Board_19-4: J1#15.3, U1#20.4 (PA1)
Board_19-5: J1#15.4, U1#20.5 (PA2)
Board_19-6: 470#17.1, J2#16.5, U1#20.6 (~RESET/PA0)
Board_19-7: J1#15.5, U1#20.7 (PA3)
Board_19-8: J2#16.1, R1#20.2, R2#19.2, U1#20.8 (GND)
Board_19-Net-(LED1-K): LED1#8.1 (K), R1#20.1
Board_19-Net-(LED2-K): LED2#12.1 (K), R2#19.1
Board_19-UPDI_RX: 470#17.2, D3#9.2 (A), J2#16.3
Board_19-UPDI_TX: D3#9.1 (K), J2#16.2

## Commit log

2024-07-16 Create LICENSE
2024-07-17 RXとTXを入れ替え。他リファクタリング。
2024-08-01 面付け基板データを追加
2024-08-01 回路図の誤記訂正
2024-08-01 READMEに使用方法を追加
2024-08-02 回路図のリファクタリング
2024-08-03 リポジトリ名称を変更
2024-12-22 ADCのサンプルコードを追加
